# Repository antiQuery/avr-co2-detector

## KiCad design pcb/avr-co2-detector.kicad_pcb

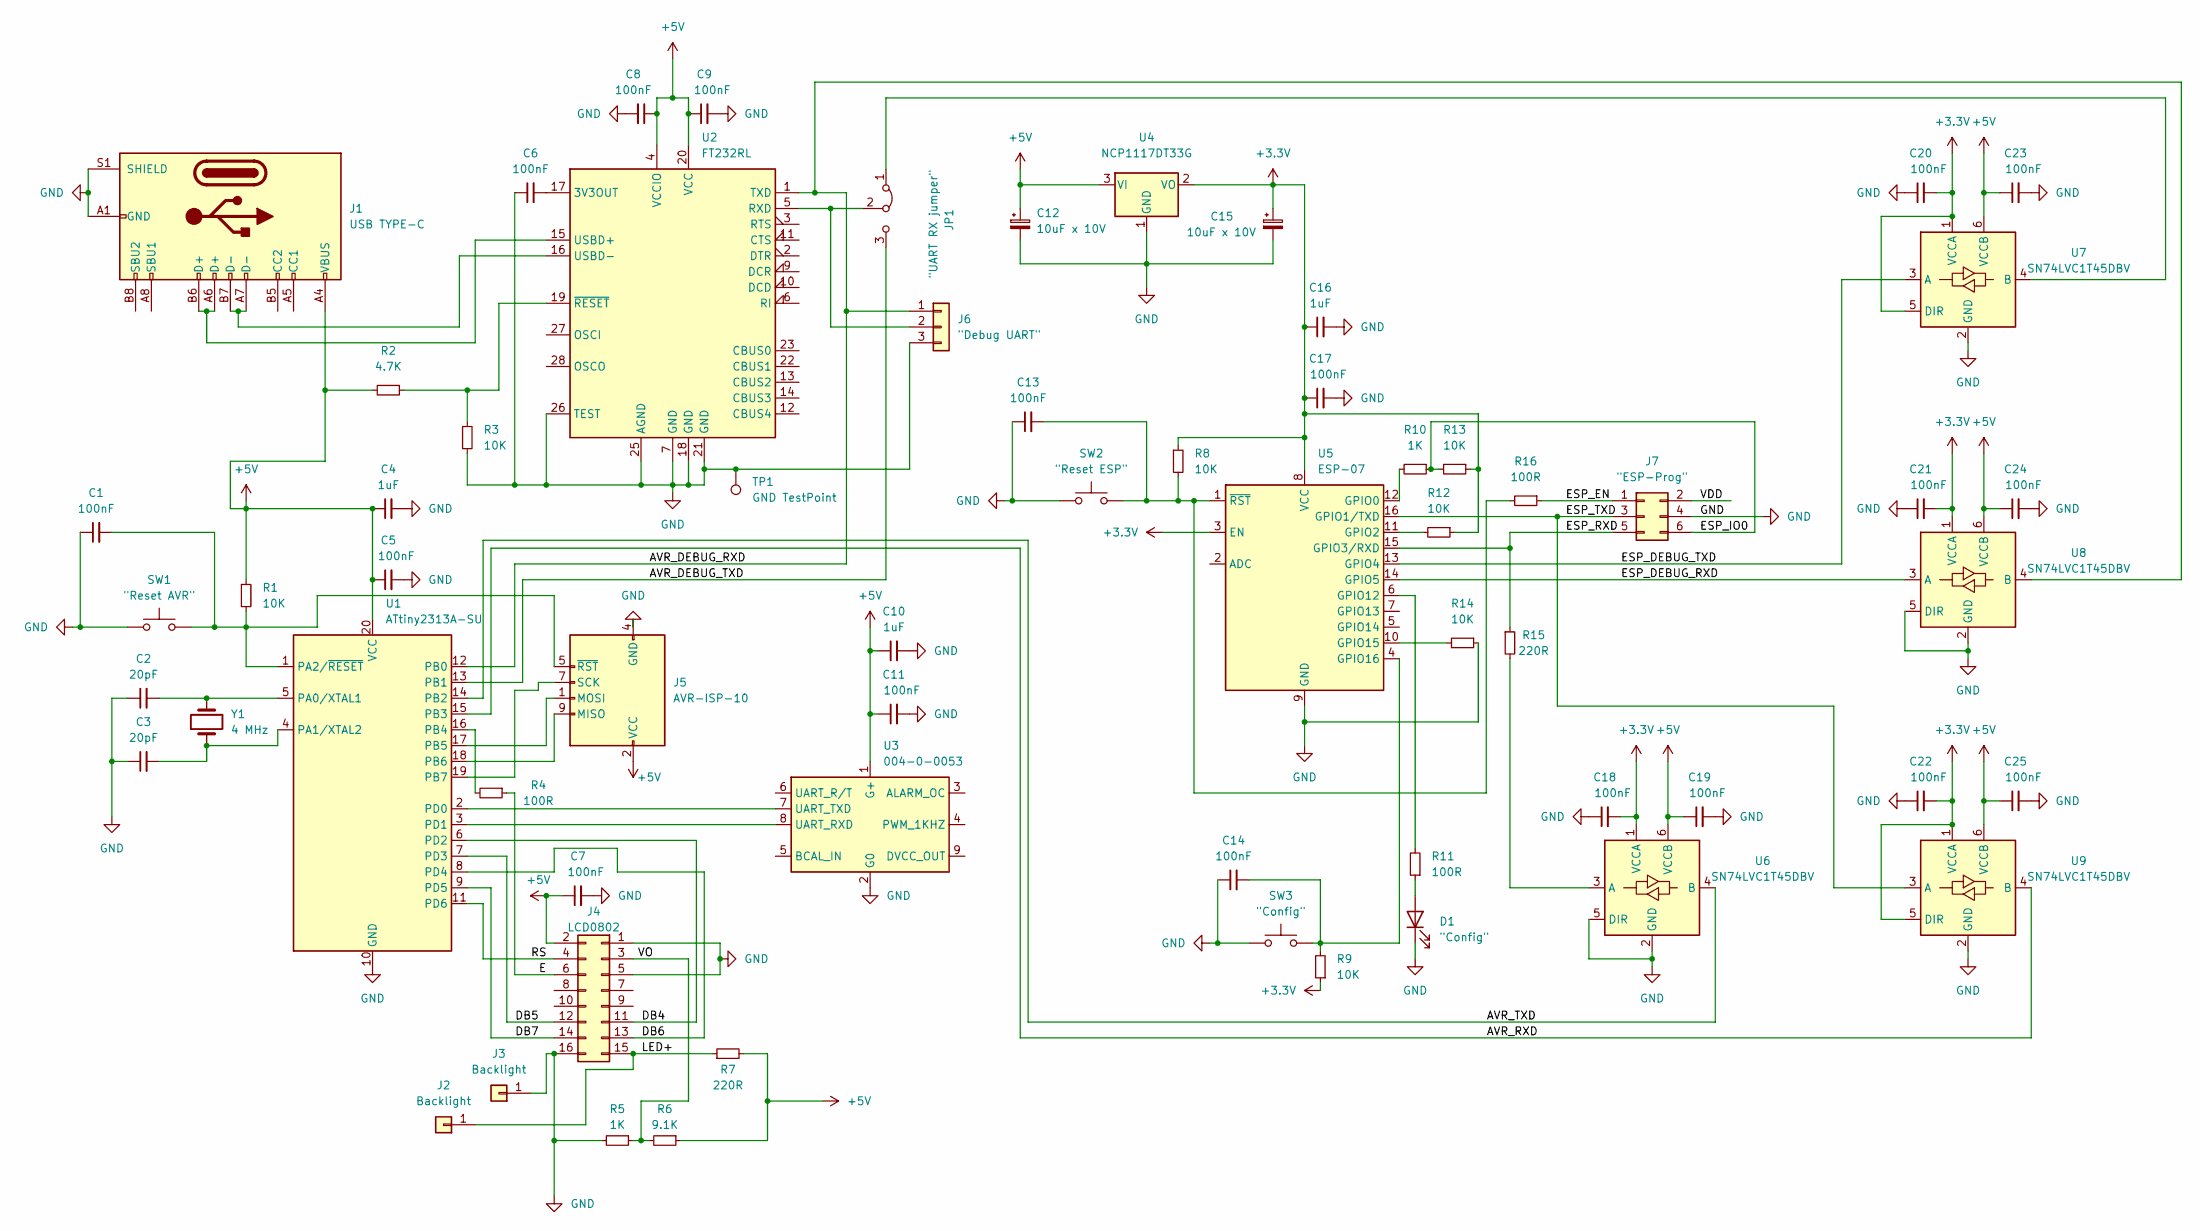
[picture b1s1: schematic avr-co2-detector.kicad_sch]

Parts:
C1, C5, C6, C7, C8, C9, C11, C13, C14, C17, C18, C19, C20, C21, C22, C23, C24, C25: 100nF; C_0805_2012Metric_Pad1.18x1.45mm_HandSolder
C2, C3: 20pF; C_0805_2012Metric_Pad1.18x1.45mm_HandSolder
C4, C10, C16: 1uF; C_0805_2012Metric_Pad1.18x1.45mm_HandSolder
C12, C15: 10uF x 10V; CP_EIA-3216-18_Kemet-A_Pad1.58x1.35mm_HandSolder
D1: "Config"; LED_D3.0mm_FlatTop
J1: USB TYPE-C; USB_C_Receptacle_HRO_TYPE-C-31-M-12
J2, J3: Backlight; PinHeader_1x01_P2.54mm_Vertical
J4: LCD0802; IDC-Header_2x08_P2.54mm_Vertical
J5: AVR-ISP-10; IDC-Header_2x05_P2.54mm_Vertical
J6: "Debug UART"; PinHeader_1x03_P2.54mm_Vertical
J7: "ESP-Prog"; PinHeader_2x03_P1.27mm_Vertical
JP1: "UART RX jumper"; PinHeader_1x03_P2.54mm_Vertical
R1, R3, R8, R9, R12, R13, R14: 10K; R_0805_2012Metric_Pad1.20x1.40mm_HandSolder
R2: 4.7K; R_0805_2012Metric_Pad1.20x1.40mm_HandSolder
R4, R11, R16: 100R; R_0805_2012Metric_Pad1.20x1.40mm_HandSolder
R5, R10: 1K; R_0805_2012Metric_Pad1.20x1.40mm_HandSolder
R6: 9.1K; R_0805_2012Metric_Pad1.20x1.40mm_HandSolder
R7, R15: 220R; R_0805_2012Metric_Pad1.20x1.40mm_HandSolder
SW1: "Reset AVR"; SW_Push_1P1T_NO_6x6mm_H9.5mm
SW2: "Reset ESP"; SW_Push_1P1T_NO_6x6mm_H9.5mm
SW3: "Config"; SW_Push_1P1T_NO_6x6mm_H9.5mm
TP1: GND TestPoint; TestPoint_Bridge_Pitch2.54mm_Drill1.0mm
U1: ATtiny2313A-SU; SOIC-20W_7.5x12.8mm_P1.27mm
U2: FT232RL; SSOP-28_5.3x10.2mm_P0.65mm
U3: 004-0-0053; Senseair_S8_Up
U4: NCP1117DT33G; TO-252-2
U5: ESP-07
U6, U7, U8, U9: SN74LVC1T45DBV; SOT-23-6
Y1: 4 MHz; Crystal_SMD_HC49-SD

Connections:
+3.3V: C15.1, C16.1, C17.1, C18.2, C20.2, C21.2, C22.2, R8.1, R9.1, R12.1, R13.1, U4.2 (VO), U5.3 (EN), U5.8 (VCC), U6.1 (VCCA), U7.1 (VCCA), U7.5 (DIR), U8.1 (VCCA), U9.1 (VCCA), U9.5 (DIR)
+5V: C4.1, C5.1, C7.1, C8.1, C9.1, C10.1, C11.1, C12.1, C19.1, C23.1, C24.1, C25.1, J1.A4 (VBUS), J1.A9 (VBUS), J1.B4 (VBUS), J1.B9 (VBUS), J4.2, J5.2 (VCC), R1.1, R2.2, R6.1, R7.2, U1.20 (VCC), U2.4 (VCCIO), U2.20 (VCC), U3.1 (G+), U4.3 (VI), U6.6 (VCCB), U7.6 (VCCB), U8.6 (VCCB), U9.6 (VCCB)
/AVR_DEBUG_RXD: J6.1, U1.12 (PB0), U2.1 (TXD), U8.4 (B)
/AVR_DEBUG_TXD: JP1.3 (B), U1.13 (PB1)
/AVR_RXD: U1.15 (PB3), U9.4 (B)
/AVR_TXD: U1.14 (PB2), U6.4 (B)
/DB4: J4.11, U1.6 (PD2)
/DB5: J4.12, U1.7 (PD3)
/DB6: J4.13, U1.8 (PD4)
/DB7: J4.14, U1.9 (PD5)
/E: J4.6, R4.1
/ESP_DEBUG_RXD: U5.14 (GPIO5), U8.3 (A)
/ESP_DEBUG_TXD: U5.13 (GPIO4), U7.3 (A)
/ESP_EN: J7.1, R16.1
/ESP_IO0: J7.6, R10.1, R13.2
/ESP_RXD: J7.5, R15.1, U5.15 (GPIO3/RXD)
/ESP_TXD: J7.3, U5.16 (GPIO1/TXD), U9.3 (A)
/LED+: J2.1, J4.15, R7.1
/RS: J4.4, U1.11 (PD6)
/VDD: J7.2
/VO: J4.3, R5.1, R6.2
GND: C1.1, C2.1, C3.1, C4.2, C5.2, C6.1, C7.2, C8.2, C9.2, C10.2, C11.2, C12.2, C13.1, C14.1, C15.2, C16.2, C17.2, C18.1, C19.2, C20.1, C21.1, C22.1, C23.2, C24.2, C25.2, D1.1 (K), J1.A1 (GND), J1.A12 (GND), J1.B1 (GND), J1.B12 (GND), J1.S1 (SHIELD), J3.1, J4.1, J4.5, J4.16, J5.4 (GND), J5.6 (GND), J5.8 (GND), J5.10 (GND), J6.3, J7.4, R3.2, R5.2, R14.1, SW1.1, SW2.1, SW3.1, TP1.1, U1.10 (GND), U2.7 (GND), U2.18 (GND), U2.21 (GND), U2.25 (AGND), U2.26 (TEST), U3.2 (G0), U4.1 (GND), U5.9 (GND), U6.2 (GND), U6.5 (DIR), U7.2 (GND), U8.2 (GND), U8.5 (DIR), U9.2 (GND); also elsewhere on the board
unnamed: C1.2, J5.5 (~RST), R1.2, SW1.2, U1.1 (PA2/~RESET)
unnamed: C2.2, U1.5 (PA0/XTAL1), Y1.2
unnamed: C3.2, U1.4 (PA1/XTAL2), Y1.1
unnamed: C6.2, U2.17 (3V3OUT)
unnamed: C13.2, R8.2, R16.2, SW2.2, U5.1 (~RST)
unnamed 27: C14.2, R9.2, SW3.2, U5.4 (GPIO16); also elsewhere on the board
unnamed: D1.2 (A), R11.1
unnamed: J1.A6 (D+), J1.B6 (D+), U2.15 (USBD+)
unnamed: J1.A7 (D-), J1.B7 (D-), U2.16 (USBD-)
unnamed: J5.1 (MOSI), U1.17 (PB5)
unnamed: J5.7 (SCK), U1.19 (PB7)
unnamed: J5.9 (MISO), U1.18 (PB6)
unnamed: J6.2, JP1.2 (C), U2.5 (RXD)
unnamed: JP1.1 (A), U7.4 (B)
unnamed: R2.1, R3.1, U2.19 (~RESET)
unnamed: R4.2, U1.16 (PB4)
unnamed: R10.2, U5.12 (GPIO0)
unnamed: R11.2, U5.6 (GPIO12)
unnamed: R12.2, U5.11 (GPIO2)
unnamed: R14.2, U5.10 (GPIO15)
unnamed: R15.2, U6.3 (A)
unnamed: U1.2 (PD0), U3.7 (UART_TXD)
unnamed: U1.3 (PD1), U3.8 (UART_RXD)

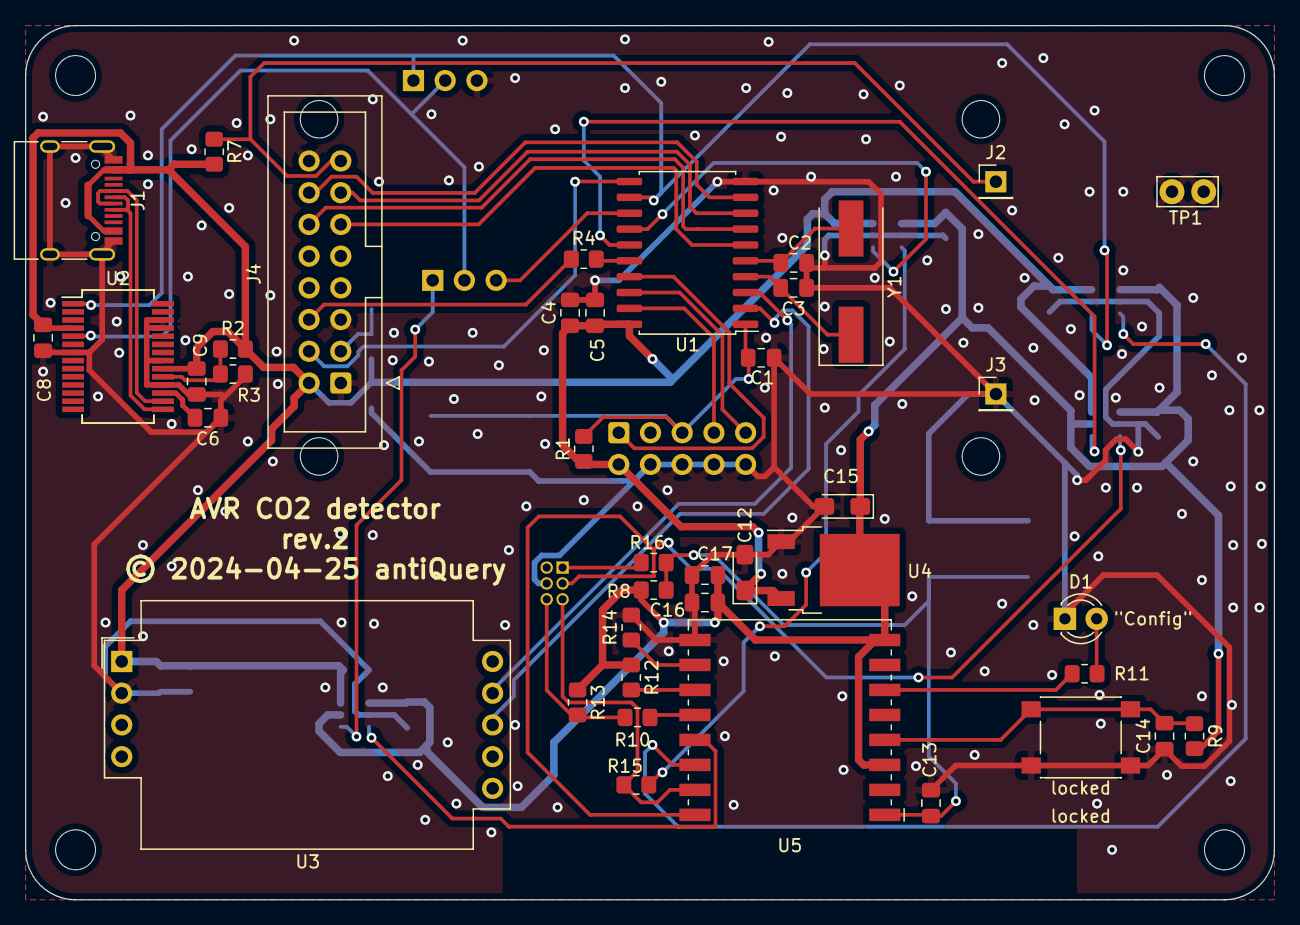
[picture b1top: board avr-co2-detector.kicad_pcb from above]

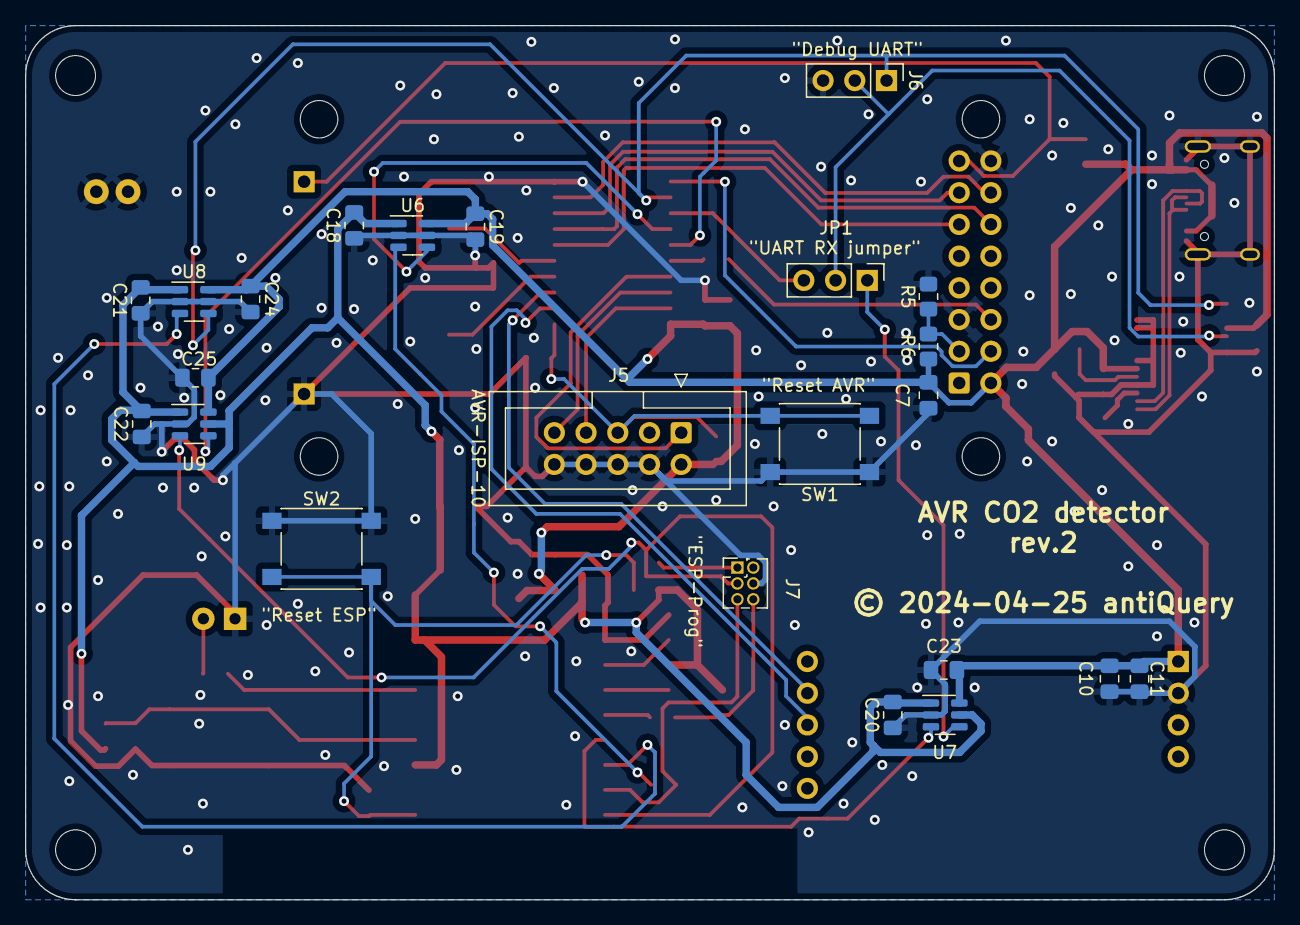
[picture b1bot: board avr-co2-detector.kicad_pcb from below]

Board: 2 copper layers, 100.0 x 70.0 mm, 65 parts (23 on the bottom side), 44 nets.

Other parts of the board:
locked: MountingHole_3.2mm_M3
locked#2: locked; SW_Push_1P1T_NO_6x6mm_H9.5mm

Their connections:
GND: locked#2.1; also elsewhere on the board
unnamed 27: locked#2.2; also elsewhere on the board

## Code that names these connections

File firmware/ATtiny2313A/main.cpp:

#include <pins_arduino.h>
#include <LiquidCrystal.h>
#include <string.h>
#include <SendOnlySoftwareSerial.h> //for send only
#include <util/delay.h>

// RS, E, DB4, DB5, DB6, DB7
LiquidCrystal lcd(PIN_PD6, PIN_PB4, PIN_PD2, PIN_PD3, PIN_PD4, PIN_PD5);

SendOnlySoftwareSerial mySerial(PIN_PB2);  // Tx pin

uint8_t cmd_s8[7] = {0xFE, 0x44, 0x00, 0x08, 0x02, 0x9F, 0x25};

unsigned short sendRequest_s8() {
    uint8_t response_s8[] = {0, 0, 0, 0, 0, 0, 0};
    
    for (int i = 0; i < 7; i++) {
        while ((UCSRA & 0x20) != 0x20) { //wait for high UDRE bit
        }
        
        UDR = cmd_s8[i];
    }
    
    int i = 0;
    while(i < 7) {
        if ((UCSRA & 0x80) == 0x80) { //wait for high RXC bit
            response_s8[i] = UDR;
            i++;
        }
    }
    
    uint8_t high = response_s8[3];
    uint8_t low = response_s8[4];
 
    unsigned short val = high * 256 + low;
    return val;
}

void loop() {
    char rate[9];
    
    unsigned short s8_co2 = sendRequest_s8();
    
    lcd.clear();
    itoa(s8_co2, rate, 10);
    strcat(rate, " ppm");
    lcd.print(rate);
    
    if (s8_co2 >= 1200) {
        strcpy(rate, "BAD");
        mySerial.write('2'); //send BAD message to ESP-07
    }
    else if (s8_co2 > 600 && s8_co2 < 1200) {
        strcpy(rate, "OK");
        mySerial.write('1'); //send OK message to ESP-07
    } 
    else {
        strcpy(rate, "FINE");
        mySerial.write('0'); //send FINE message to ESP-07
    }
    
    lcd.setCursor(0, 1);
    strcat(rate, " CO2");
    lcd.print(rate);
    
    _delay_ms(1000);
}

int main() {
    //Initialize Hardware UART for receive from SenseAir S8
    UCSRB = UCSRB | 0x18; //Enable Receive and Transmit (set RXEN, TXEN bit)
    UBRRL = 25; // u2x = 0; fosc = 4.0000 MHz; Baud Rate = 9600 => ubrr = 25
    
    lcd.begin(8, 2);
    
    mySerial.begin(9600);
    
    while (true) {
        loop();
    }
}

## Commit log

2023-12-19 added Arduino UNO based schematic designed in Fritzing
2023-12-22 move Senseair_s8_lcd.fzz to arduino-prototype directory
2023-12-22 added arduino project
2024-01-21 added esp8266 web page to configure wifi
2024-02-27 Implemented writing/reading to/from EEPROM (ssid, password)
2024-03-14 Added initial version of KiCad project of avr co2 detector (microcontroller, XTAL, reset circuit)
2024-03-15 Added USB Type-C connector for power supply, decoupling capacitor for ATtiny2313A
2024-03-19 Added voltage regulator (3.3V) and ESP-07 module
2024-03-20 Added reset circuit and connector for programming ESP-07
2024-03-20 Added NodeMCU V3 and logic level converter to Fritzing schematic
2024-03-20 Added level shifters for ESP-07 UART
2024-03-21 Added connector for programming ATtiny2313A
2024-03-23 Added connector for LCD
2024-03-27 Changed symbol Connector:USB_C_Receptacle_PowerOnly_6P to Connector:USB_C_Receptacle_USB2.0
2024-03-27 Added USB to serial UART interface for debugging ATtiny2313A
2024-03-29 Added Senseair S8, connected ESP-07 UART to ATtiny2313A
2024-03-29 Added configuration LED and button, debug UART RX jumper
2024-04-01 Added level shifters for ESP-07 debug UART
2024-04-01 Annotated all parts, assigned all footprints, exported to pcb
2024-04-06 Placed PCB outline, mounting holes, LCD connector, config button and LED, USB Type-C connector, SenseAir S8
2024-04-06 Added connectors for LCD backlight
2024-04-09 Initially placed parts and routed PCB
2024-04-11 Corrected pull-up voltage on resistor R9, corrected footprint for connector J6
2024-04-11 Finished routing
2024-04-12 Added GND polygons
2024-04-12 Fixed DRC errors and warnings
2024-04-14 Added PCB description to silkscreen, rounded PCB corners, generated Gerber and drill files
2024-04-24 Fixed LCD connector pinout, corrected resistor R16 connection
2024-04-24 Increased width of traces of 3.3V and 5V, mirrored project info on silkscreen, added "Debug UART" connector
2024-04-25 Added GND TestPoint, assigned revision 2, updated Gerber and drill files
2024-04-25 Corrected silkscreen, updated Gerber and drill files
2024-05-14 Added src files of LiquidCrystal library (https://github.com/arduino-libraries/LiquidCrystal.git, sha-1 2d704b6d7f688cc1fb626cb937fd5ef5d5e33c4d)
2024-05-14 Added selected src files of ATTinyCore library (https://github.com/SpenceKonde/ATTinyCore.git, sha-1 c0b7e78f750111bbfeeb36088ef9be3d5728a927)
2024-05-14 Implemented Makefile and main.cpp (testing LCD0802) for ATtiny2313
2024-05-14 Commented not used functions in Print.cpp for memory size optimization
2024-05-18 Added src files of SendOnlySoftwareSerial library (https://github.com/nickgammon/SendOnlySoftwareSerial.git, sha-1 a1d3d44110a61ee3ef2780dc5b24f2ae7b1e324d)
2024-05-18 Applied SendOnlySoftwareSerial library
2024-05-21 Supported Hardware UART for communicating with SenseAir S8
2024-05-22 Modified LiquidCrystal and SendOnlySoftwareSerial libraries for memory size optimization; Supported Software UART for sending messages to ESP-07
